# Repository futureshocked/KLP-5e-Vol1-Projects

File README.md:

# KiCad Like a Pro, 5th Edition: Volume 1 project files

These are the finished KiCad projects from **Volume 1, Getting Started: Your First PCBs**, part of
*KiCad Like a Pro, 5th Edition* by Peter Dalmaris. The book teaches by building, and this repository
holds the result of each build, so you can open a working project, compare it against your own, or
pick up where you got stuck.

Book page and table of contents: <https://techexplorations.com/kicad/book/>

## Projects

| Folder | Project | Book chapter | Board |
|---|---|---|---|
| [`ch02-blinky/`](ch02-blinky/) | A 555 LED blinker, the project from the hands-on tour | Chapters 2 and 3 | 2-layer through-hole |
| [`ch08-breadboard-psu/`](ch08-breadboard-psu/) | Breadboard power supply with a USB-C input | Chapter 8 | 2-layer, through-hole and SMD |
| [`ch09-solar-psu/`](ch09-solar-psu/) | Tiny solar power supply (a rebuild of the Elektor design by Clemens Valens) | Chapter 9 | 2-layer, through-hole and SMD |

## How to use them

1. Install KiCad 10 from <https://www.kicad.org/download/>. The projects were made with KiCad 10, and
   older versions may not open them.
2. Clone this repository, or download it as a ZIP with the green **Code** button.
3. In KiCad's project manager choose **File, Open Project**, and open the `.kicad_pro` file inside
   the project folder you want.

Each project folder is self-contained. The `ch08` and `ch09` projects keep their imported parts in a
local `Libraries/` folder, and their library tables point at it with `${KIPRJMOD}`, so nothing
needs installing.

### What each folder holds

```
chNN-<project>/
├── <project>.kicad_pro / .kicad_sch / .kicad_pcb   the project, schematic and board
├── Gerbers/        manufacturing files: Gerber layers, one Excellon drill file, and the job file
├── BOM/            the bill of materials exported from the schematic
└── Libraries/      imported symbols, footprints and 3D models (ch08 and ch09)
```

The files in `Gerbers/` are ready to upload to a PCB manufacturer. The drill file is a single Excellon
file in millimetres with decimal coordinates, a format that fabricators such as NextPCB accept.
Chapter 10 of the book explains how it was produced and why that format matters.

### 3D models in the blinker

The blinker board refers to KiCad's standard 3D models through the `${KICAD10_3DMODEL_DIR}`
variable, which KiCad 10 sets for you. If the 3D viewer shows a bare board, open
**Preferences, Configure Paths** and check that the variable points at KiCad's `3dmodels` folder.

## If your result differs from the book

The projects here are the author's finished versions. Your own may look a little different, and
that is normal. Differences in placement and routing are fine as long as the design rules check
(DRC and ERC) passes. If a project does not open, or something does not match the chapter, please
open an issue on this repository.

## Licence and credits

The project files written for the book are released under the [MIT licence](LICENSE).

1. The solar power supply is a rebuild of the **Tiny Solar Supply** by Clemens Valens, published by
   Elektor. Credit for the circuit belongs to its author.
2. The files in `ch08-breadboard-psu/Libraries/` and `ch09-solar-psu/Libraries/` (symbols,
   footprints and 3D models for the USB-C receptacle, slide switch, AP3015A, SS14 diode, inductor and
   fuse) come from the parts' manufacturers and from SnapMagic, and they stay under their own terms.
   The MIT licence does not cover them.

## The rest of the series

Volume 2 of the book has its own project repository. See the book page above for the other volumes
and for the video courses.

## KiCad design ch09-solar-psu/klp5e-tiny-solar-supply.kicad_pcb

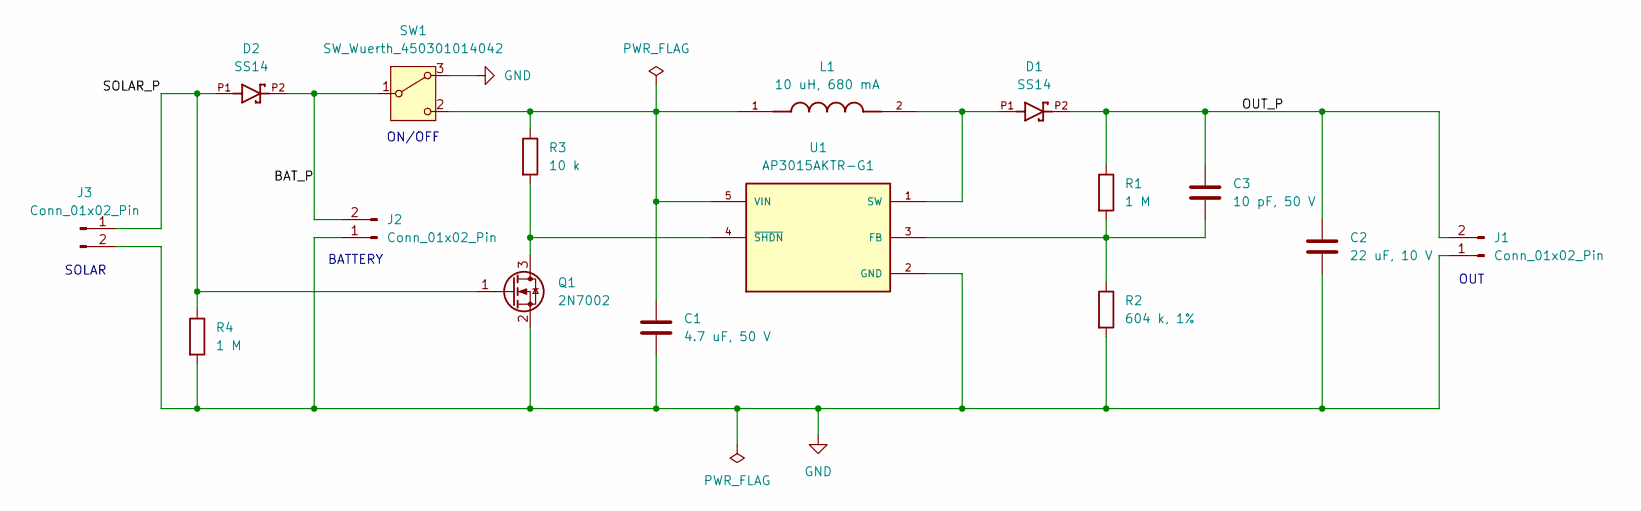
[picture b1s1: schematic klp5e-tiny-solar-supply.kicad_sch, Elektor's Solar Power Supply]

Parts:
C1: 4.7 uF, 50 V; C_Disc_D5.0mm_W2.5mm_P2.50mm
C2: 22 uF, 10 V; C_Radial_D5.0mm_H11.0mm_P2.00mm
C3: 10 pF, 50 V; C_Disc_D5.0mm_W2.5mm_P2.50mm
D1, D2: SS14; SMA
J1, J2, J3: Conn_01x02_Pin; PinHeader_1x02_P2.54mm_Vertical
L1: 10 uH, 680 mA; IND_ASPI-0630LR-100M-T15; PARTREV B
Q1: 2N7002; SOT-23
R1, R4: 1 M; R_Axial_DIN0204_L3.6mm_D1.6mm_P5.08mm_Horizontal
R2: 604 k, 1%; R_Axial_DIN0204_L3.6mm_D1.6mm_P5.08mm_Horizontal
R3: 10 k; R_Axial_DIN0204_L3.6mm_D1.6mm_P5.08mm_Horizontal
SW1: SW_Wuerth_450301014042; SW_Slide-03_Wuerth-WS-SLTV_10x2.5x6.4_P2.54mm
U1: AP3015AKTR-G1; SOT95P280X145-5N; PARTREV 1.4

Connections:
/BAT_P: D2.P2, J2.2, SW1.1 (B)
/OUT_P: C2.1, C3.1, D1.P2, J1.2, R1.1
/SOLAR_P: D2.P1, J3.1, Q1.1 (G), R4.1
GND: C1.2, C2.2, J1.1, J2.1, J3.2, Q1.2 (S), R2.2, R4.2, SW1.3 (A), U1.2 (GND)
unnamed: Q1.3 (D), R3.2, U1.4 (~SHDN)
unnamed: C1.1, L1.1, R3.1, SW1.2 (C), U1.5 (VIN)
unnamed: C3.2, R1.2, R2.1, U1.3 (FB)
unnamed: D1.P1, L1.2, U1.1 (SW)

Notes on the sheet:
SOLAR
ON/OFF
BATTERY
OUT

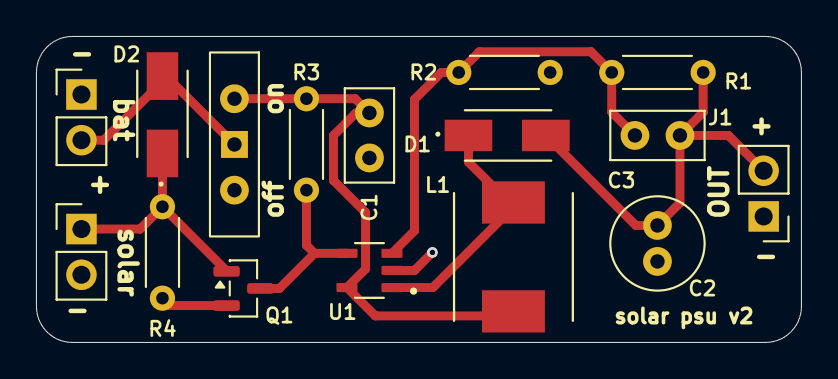
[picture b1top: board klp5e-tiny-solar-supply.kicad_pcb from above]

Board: 2 copper layers, 42.5 x 17.0 mm, 16 parts (0 on the bottom side), 8 nets.

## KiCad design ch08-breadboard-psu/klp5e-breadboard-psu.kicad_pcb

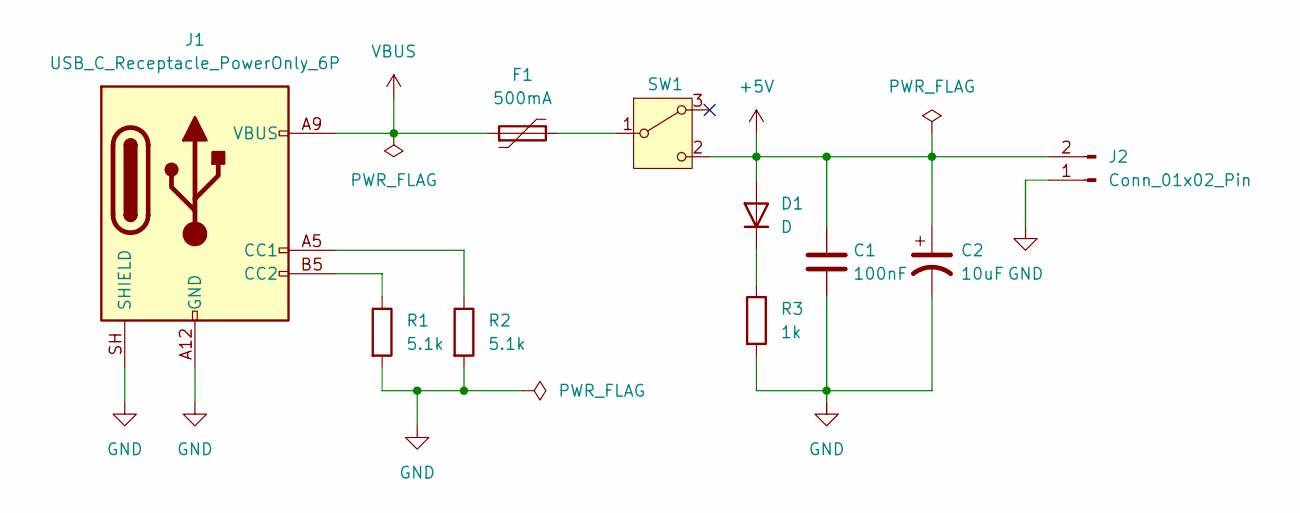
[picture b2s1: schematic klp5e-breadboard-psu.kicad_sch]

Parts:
C1: 100nF; C_Disc_D3.0mm_W1.6mm_P2.50mm
C2: 10uF; CP_Radial_D4.0mm_P1.50mm
D1: D; LED_D5.0mm
F1: 500mA; Fuse_Bourns_MF-RHT050
J1: USB_C_Receptacle_PowerOnly_6P; USB_C_Receptacle_GCT_USB4125-xx-x-0190_6P_TopMnt_Horizontal
J2: Conn_01x02_Pin; PinHeader_1x02_P2.54mm_Vertical
R1, R2: 5.1k; R_Axial_DIN0204_L3.6mm_D1.6mm_P5.08mm_Horizontal
R3: 1k; R_Axial_DIN0204_L3.6mm_D1.6mm_P5.08mm_Horizontal
SW1: SW_Wuerth_450301014042; SW_Slide-03_Wuerth-WS-SLTV_10x2.5x6.4_P2.54mm

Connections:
+5V: C1.1, C2.1, D1.2 (A), J2.2, SW1.2 (C)
GND: C1.2, C2.2, J1.A12 (GND), J1.B12 (GND), J1.SH (SHIELD), J2.1, R1.2, R2.2, R3.2
unnamed: D1.1 (K), R3.1
unnamed: J1.A5 (CC1), R2.1
unnamed: J1.B5 (CC2), R1.1
unnamed: F1.2, SW1.1 (B)
VBUS: F1.1, J1.A9 (VBUS), J1.B9 (VBUS)

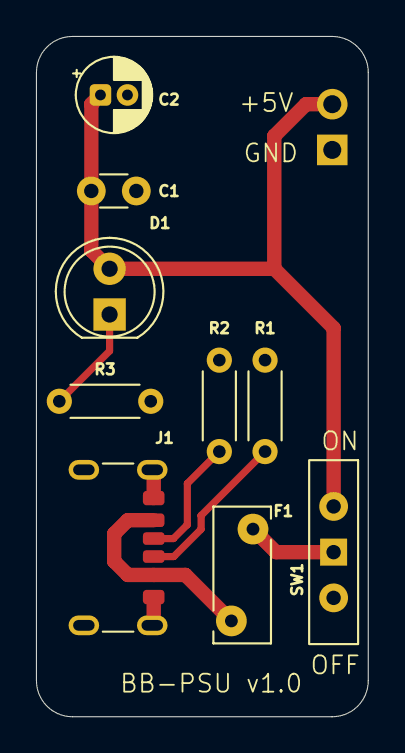
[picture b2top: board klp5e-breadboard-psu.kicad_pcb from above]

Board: 2 copper layers, 18.4 x 37.8 mm, 10 parts (1 on the bottom side), 7 nets.

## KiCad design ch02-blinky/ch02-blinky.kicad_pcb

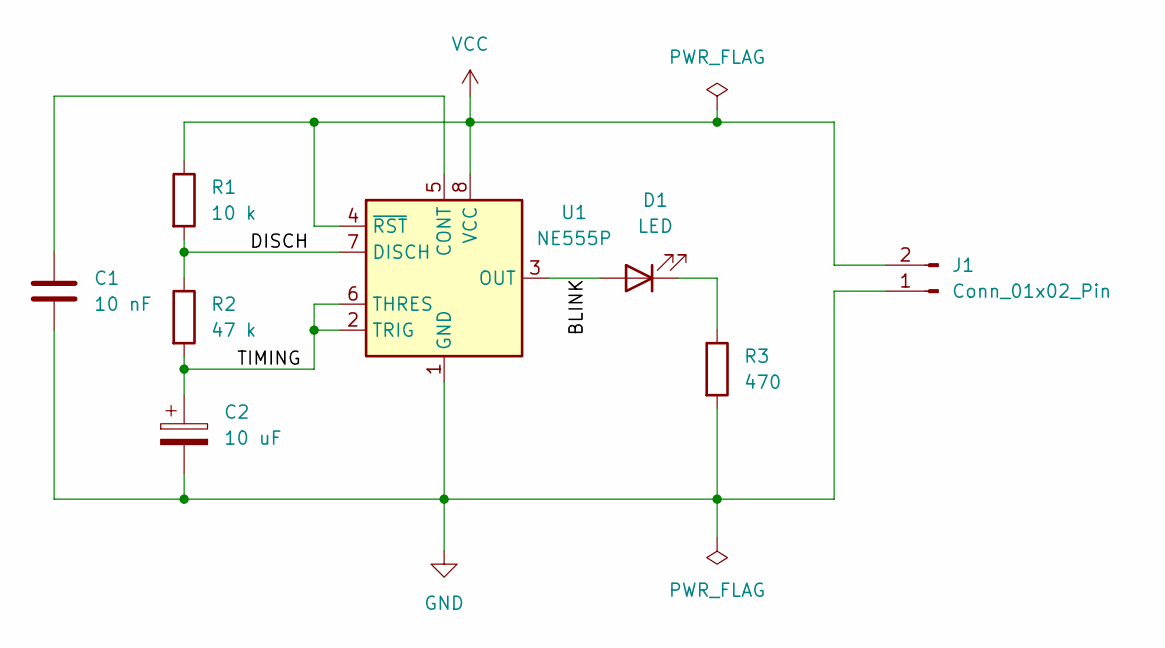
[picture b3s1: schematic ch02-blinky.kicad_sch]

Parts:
C1: 10 nF; C_Disc_D3.0mm_W2.0mm_P2.50mm
C2: 10 uF; C_Radial_D4.0mm_H5.0mm_P1.50mm
D1: LED; LED_D5.0mm
J1: Conn_01x02_Pin; PinHeader_1x02_P2.54mm_Vertical
R1: 10 k; R_Axial_DIN0204_L3.6mm_D1.6mm_P5.08mm_Horizontal
R2: 47 k; R_Axial_DIN0204_L3.6mm_D1.6mm_P5.08mm_Horizontal
R3: 470; R_Axial_DIN0204_L3.6mm_D1.6mm_P5.08mm_Horizontal
U1: NE555P; DIP-8_W7.62mm

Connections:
/BLINK: D1.2 (A), U1.3 (OUT)
/DISCH: R1.2, R2.1, U1.7 (DISCH)
/TIMING: C2.1, R2.2, U1.2 (TRIG), U1.6 (THRES)
GND: C1.2, C2.2, J1.1, R3.2, U1.1 (GND)
unnamed: D1.1 (K), R3.1
unnamed: C1.1, U1.5 (CONT)
VCC: J1.2, R1.1, U1.4 (~RST), U1.8 (VCC)

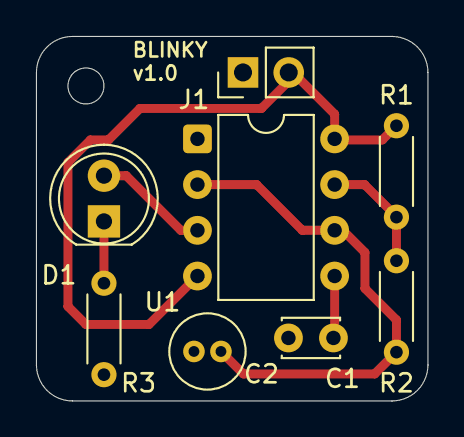
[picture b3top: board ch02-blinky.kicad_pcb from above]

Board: 2 copper layers, 21.8 x 20.2 mm, 8 parts (0 on the bottom side), 7 nets.
